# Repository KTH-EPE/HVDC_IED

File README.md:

# HVDC_IED
software and hardware for HVDC IED lab prototype

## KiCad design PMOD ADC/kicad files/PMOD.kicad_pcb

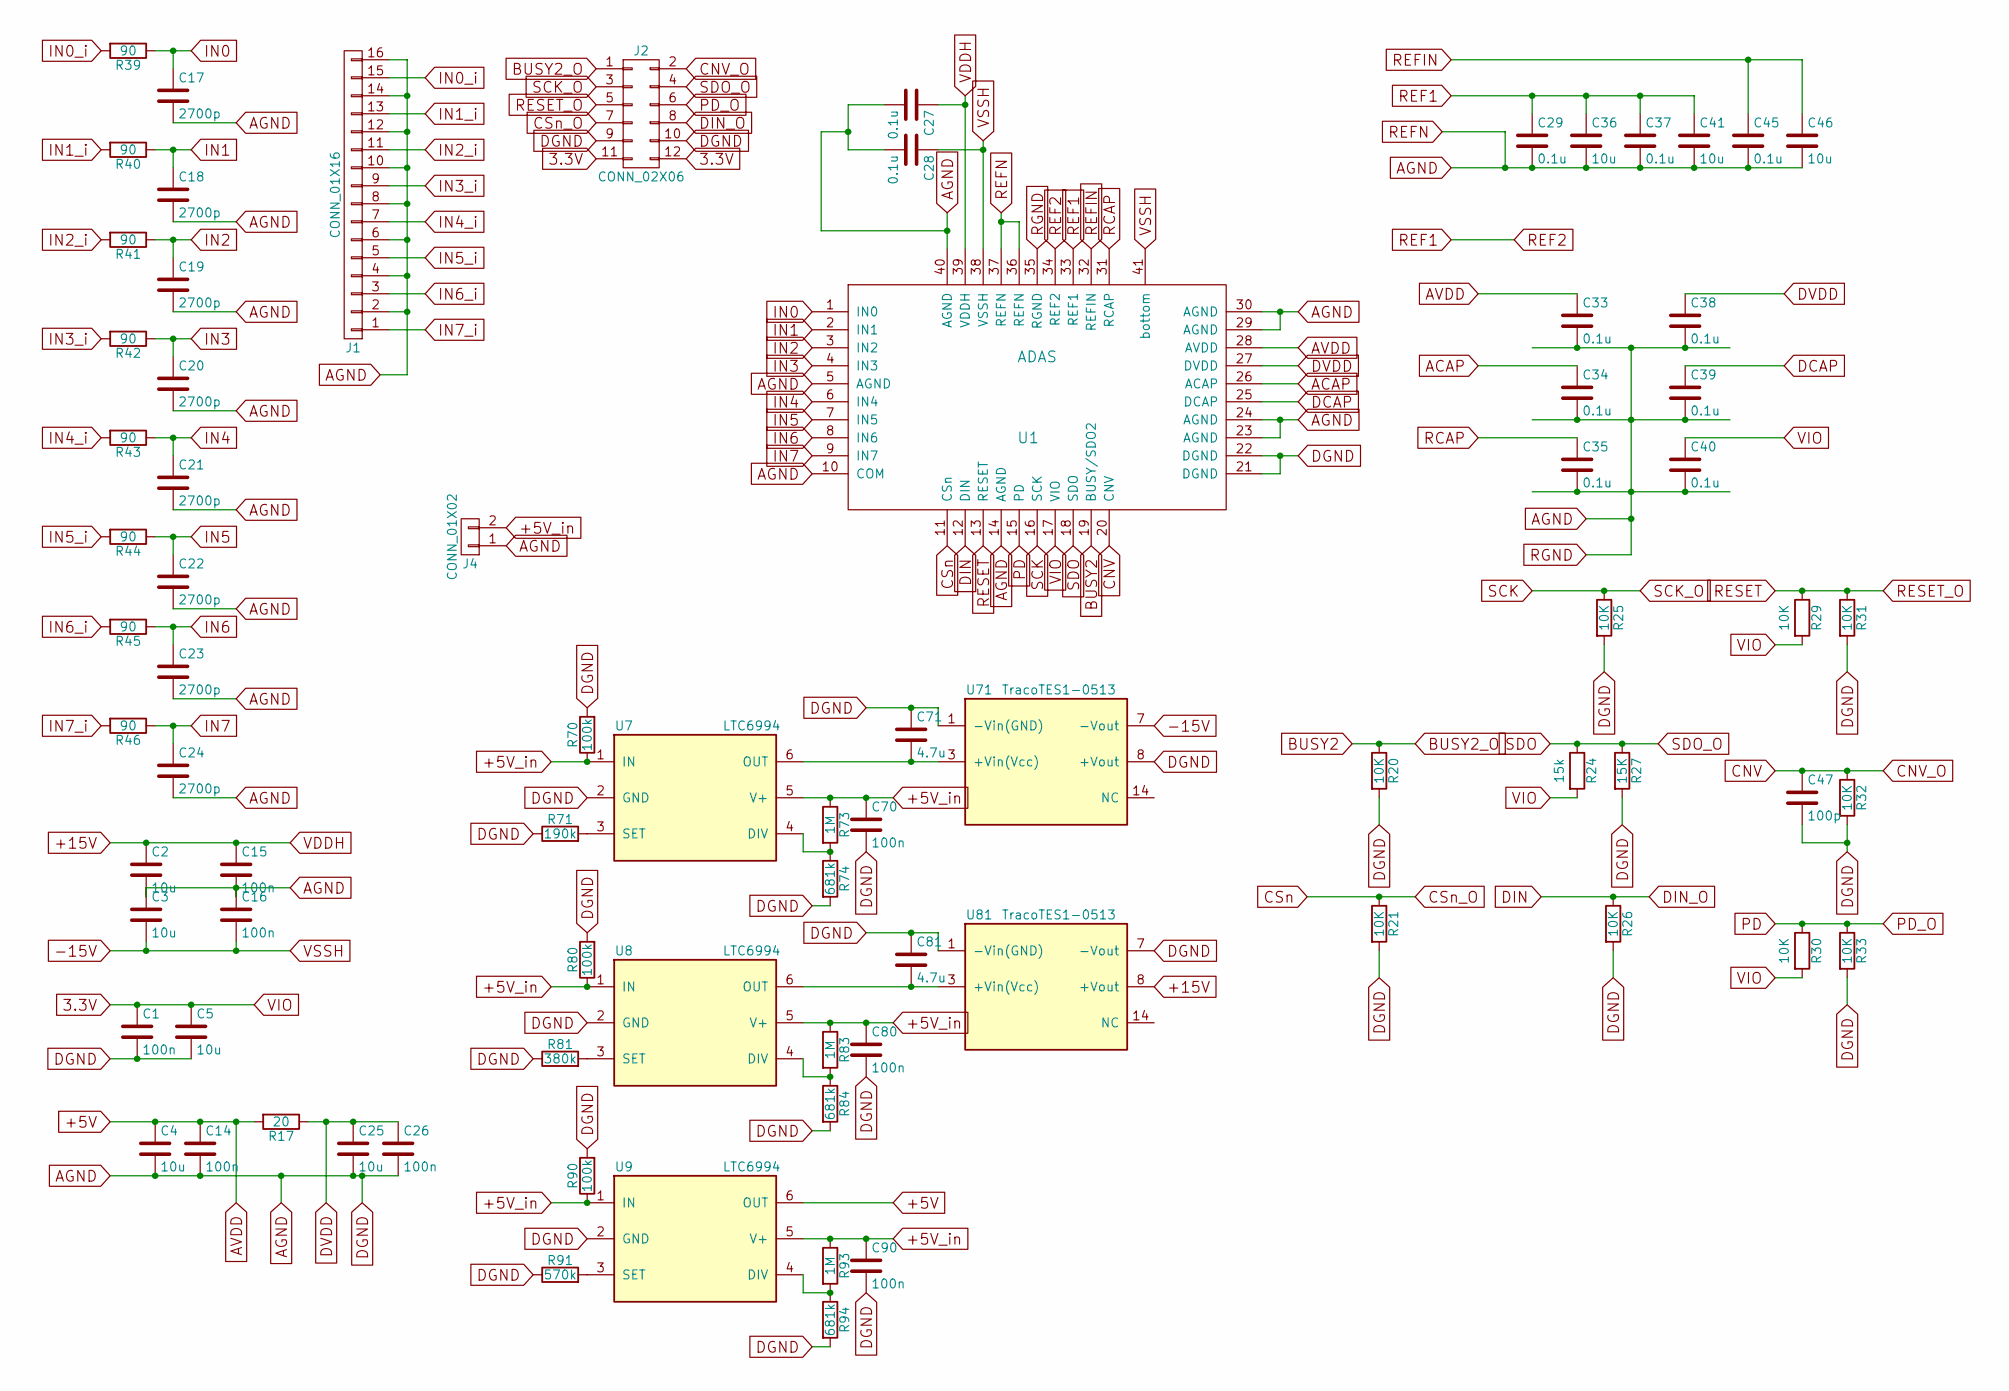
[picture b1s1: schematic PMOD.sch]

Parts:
C1, C14, C15, C16, C26, C70, C80, C90: 100n; C_1206_HandSoldering
C2, C3, C4, C5, C25, C36, C41, C46: 10u; C_1206_HandSoldering
C17, C18, C19, C20, C21, C22, C23, C24: 2700p; C_1206_HandSoldering
C27, C28, C29, C33, C34, C35, C37, C38, C39, C40, C45: 0.1u; C_1206_HandSoldering
C47: 100p; C_1206_HandSoldering
C71, C81: 4.7u; C_1206_HandSoldering
J1: CONN_01X16; Pin_Header_Angled_1x16_Pitch2.54mm
J2: CONN_02X06; Multicomp_MC9A_2x06x2.54mm_Straight
J4: CONN_01X02; Pin_Header_Angled_1x02_Pitch2.54mm
R17: 20; R_0603_HandSoldering
R20, R21, R25, R26, R29, R30, R31, R32, R33: 10K; R_0603_HandSoldering
R24: 15k; R_0603_HandSoldering
R27: 15K; R_0603_HandSoldering
R39, R40, R41, R42, R43, R44, R45, R46: 90; R_0603_HandSoldering
R70, R80, R90: 100k; R_0603_HandSoldering
R71: 190k; R_0603_HandSoldering
R73, R83, R93: 1M; R_0603_HandSoldering
R74, R84, R94: 681k; R_0603_HandSoldering
R81: 380k; R_0603_HandSoldering
R91: 570k; R_0603_HandSoldering
U1: ADAS; QFN-40-1EP_6x6mm_Pitch0.5mm
U7, U8, U9: LTC6994; TSOT-23-6_HandSoldering
U71, U81: TracoTES1-0513; DCDC-Conv_TRACO_TES-1SM

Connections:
3.3V: C1.1, C5.1, C40.1, J2.11, J2.12, R24.2, R29.2, R30.2, U1.17 (VIO)
+5V: C4.1, C14.1, C33.1, R17.2, U1.28 (AVDD), U9.6 (OUT)
+5V_in: C70.1, C80.1, C90.1, J4.2, R70.1, R73.1, R80.1, R83.1, R90.1, R93.1, U7.1 (IN), U7.5 (V+), U8.1 (IN), U8.5 (V+), U9.1 (IN), U9.5 (V+)
+15V: C2.1, C15.1, C27.1, U1.39 (VDDH), U81.8 (+Vout)
-15V: C3.2, C16.2, C28.1, U1.38 (VSSH), U1.41 (bottom), U71.7 (-Vout)
ACAP: C34.1, U1.26 (ACAP)
AGND: C1.2, C2.2, C3.1, C4.2, C5.2, C14.2, C15.2, C16.1, C17.2, C18.2, C19.2, C20.2, C21.2, C22.2, C23.2, C24.2, C25.2, C26.2, C27.2, C28.2, C29.2, C33.2, C34.2, C35.2, C36.2, C37.2, C38.2, C39.2, C40.2, C41.2, C45.2, C46.2, C47.2, C70.2, C71.1, C80.2, C81.1, C90.2, J1.2, J1.4, J1.6, J1.8, J1.10, J1.12, J1.14, J1.16, J2.9, J2.10, J4.1, R20.2, R21.2, R25.2, R26.2, R27.2, R31.2, R32.2, R33.2, R70.2, R71.1, R74.2, R80.2, R81.1, R84.2, R90.2, R91.1, R94.2, U1.5 (AGND), U1.10 (COM), U1.14 (AGND), U1.21 (DGND), U1.22 (DGND), U1.23 (AGND), U1.24 (AGND), U1.29 (AGND), U1.30 (AGND), U1.35 (RGND), U1.36 (REFN), U1.37 (REFN), U1.40 (AGND), U7.2 (GND), U8.2 (GND), U9.2 (GND), U71.1 (-Vin(GND)), U71.8 (+Vout), U81.1 (-Vin(GND)), U81.7 (-Vout)
BUSY2: J2.1, R20.1, U1.19 (BUSY/SDO2)
CNV: C47.1, J2.2, R32.1, U1.20 (CNV)
CSn: J2.7, R21.1, U1.11 (CSn)
DCAP: C39.1, U1.25 (DCAP)
DIN: J2.8, R26.1, U1.12 (DIN)
DVDD: C25.1, C26.1, C38.1, R17.1, U1.27 (DVDD)
IN0: C17.1, R39.1, U1.1 (IN0)
IN0_i: J1.15, R39.2
IN1: C18.1, R40.1, U1.2 (IN1)
IN1_i: J1.13, R40.2
IN2: C19.1, R41.1, U1.3 (IN2)
IN2_i: J1.11, R41.2
IN3: C20.1, R42.1, U1.4 (IN3)
IN3_i: J1.9, R42.2
IN4: C21.1, R43.1, U1.6 (IN4)
IN4_i: J1.7, R43.2
IN5: C22.1, R44.1, U1.7 (IN5)
IN5_i: J1.5, R44.2
IN6: C23.1, R45.1, U1.8 (IN6)
IN6_i: J1.3, R45.2
IN7: C24.1, R46.1, U1.9 (IN7)
IN7_i: J1.1, R46.2
unnamed: C71.2, U7.6 (OUT), U71.3 (+Vin(Vcc))
unnamed: C81.2, U8.6 (OUT), U81.3 (+Vin(Vcc))
unnamed: R71.2, U7.3 (SET)
unnamed: R73.2, R74.1, U7.4 (DIV)
unnamed: R81.2, U8.3 (SET)
unnamed: R83.2, R84.1, U8.4 (DIV)
unnamed: R91.2, U9.3 (SET)
unnamed: R93.2, R94.1, U9.4 (DIV)
PD: J2.6, R30.1, R33.1, U1.15 (PD)
RCAP: C35.1, U1.31 (RCAP)
REF1: C29.1, C36.1, C37.1, C41.1, U1.33 (REF1), U1.34 (REF2)
REFIN: C45.1, C46.1, U1.32 (REFIN)
RESET: J2.5, R29.1, R31.1, U1.13 (RESET)
SCK: J2.3, R25.1, U1.16 (SCK)
SDO: J2.4, R24.1, R27.1, U1.18 (SDO)

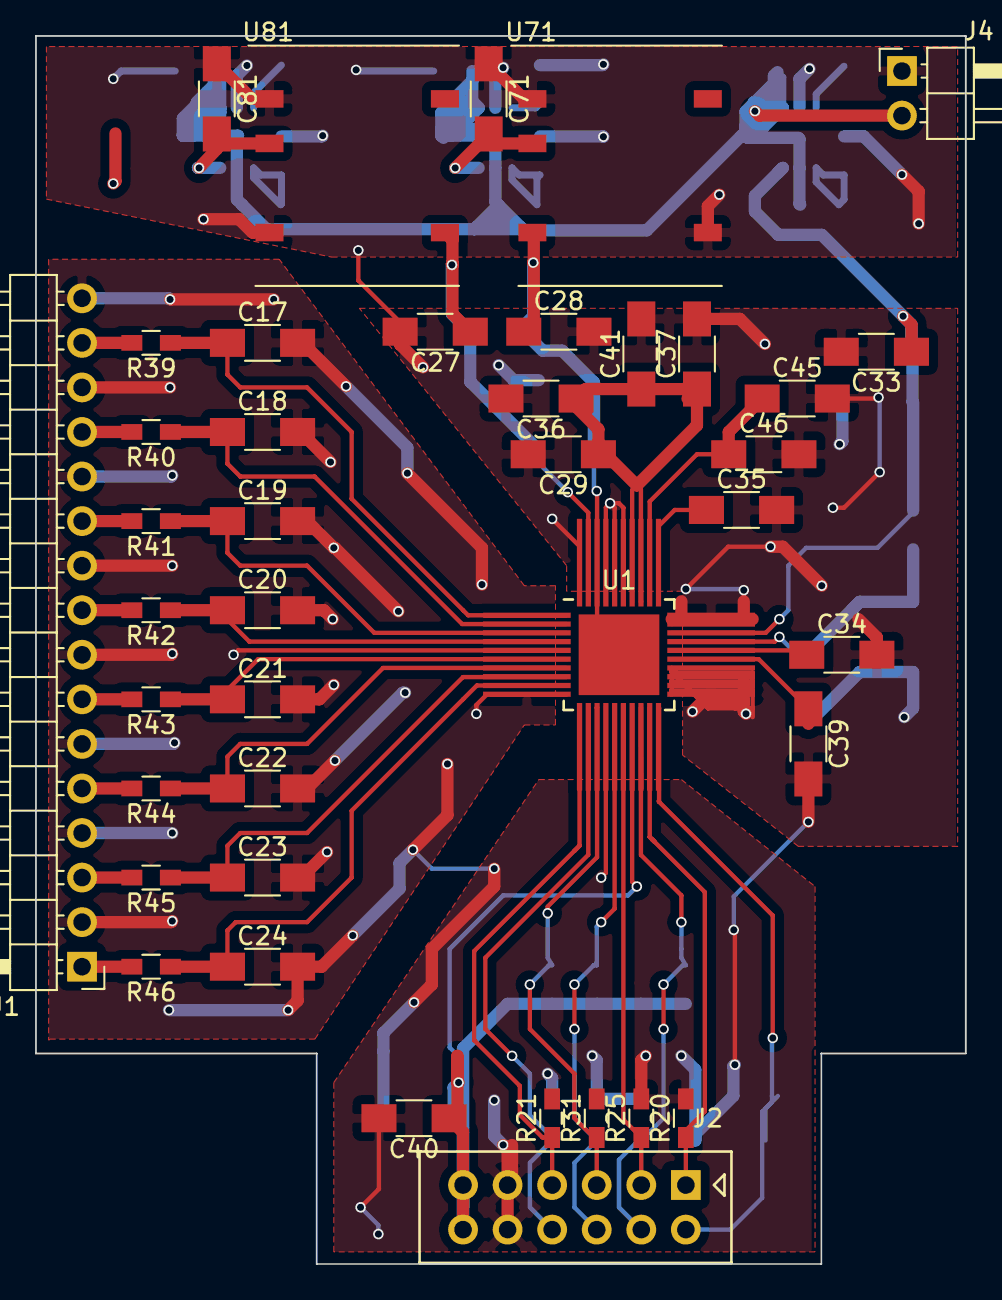
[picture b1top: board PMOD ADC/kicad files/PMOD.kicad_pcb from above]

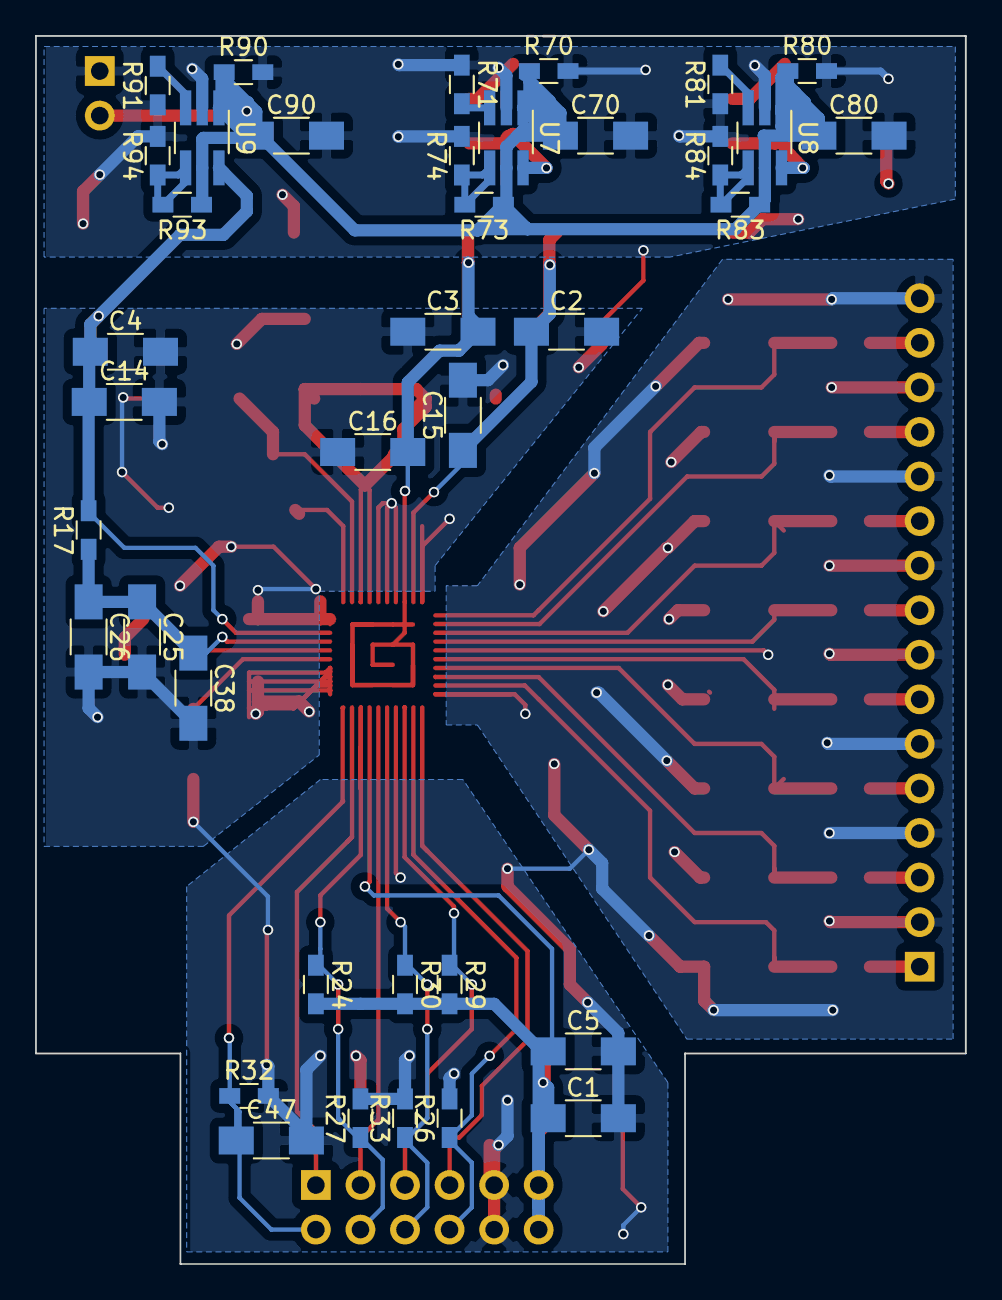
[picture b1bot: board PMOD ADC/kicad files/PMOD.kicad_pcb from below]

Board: 2 copper layers, 53.0 x 70.0 mm, 79 parts (38 on the bottom side), 44 nets.

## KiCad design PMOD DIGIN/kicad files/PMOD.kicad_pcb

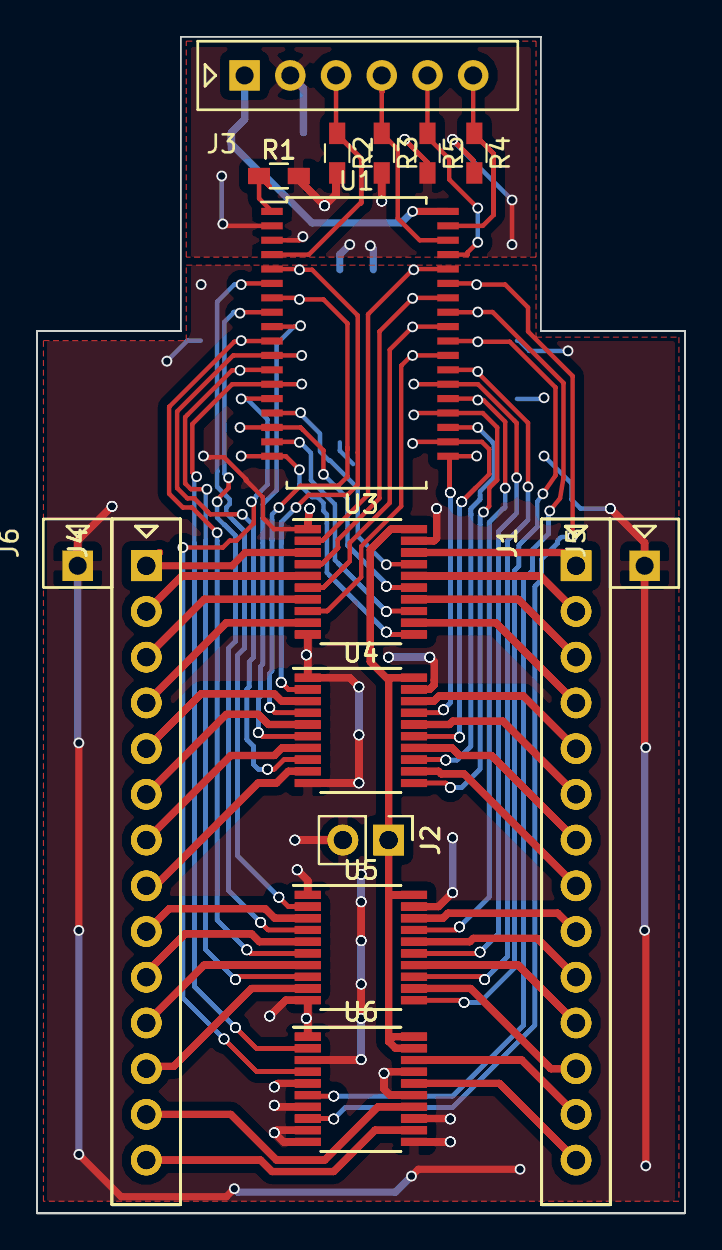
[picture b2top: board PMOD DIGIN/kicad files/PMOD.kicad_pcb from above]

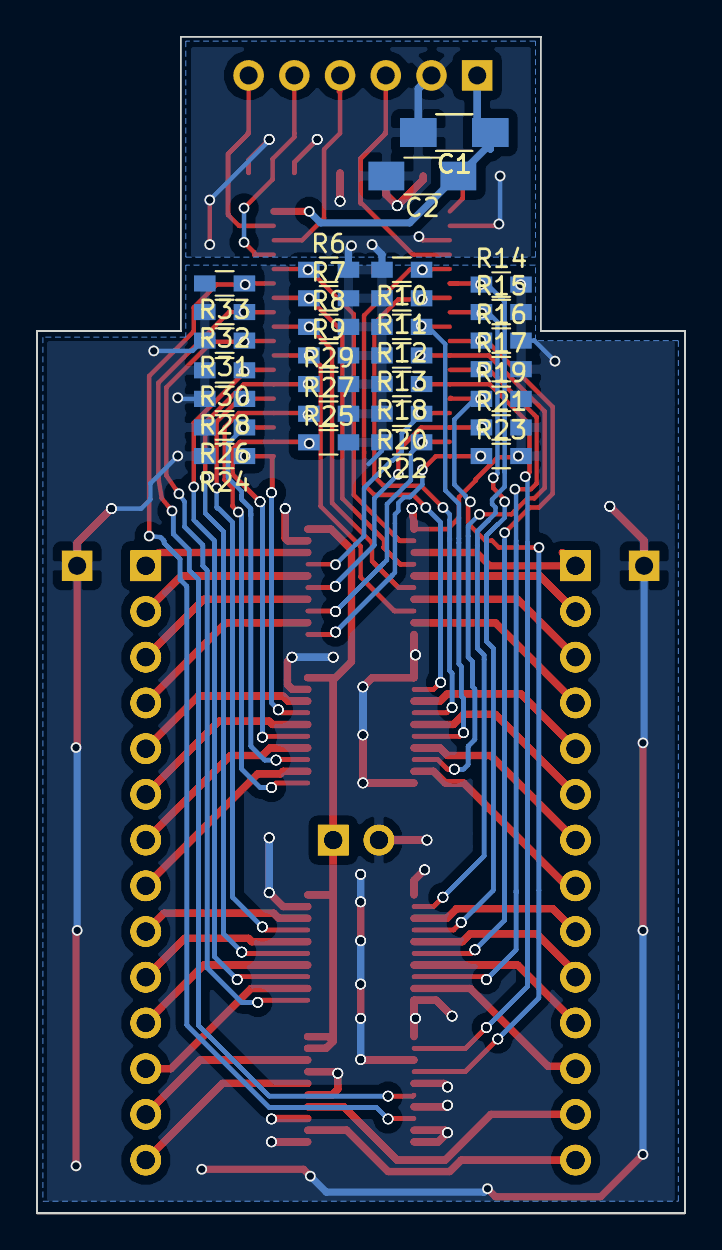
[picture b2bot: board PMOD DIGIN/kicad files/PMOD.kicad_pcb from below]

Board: 2 copper layers, 36.0 x 65.4 mm, 55 parts (31 on the bottom side), 64 nets.

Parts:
C1, C1#2: 1u; C_1206_HandSoldering
C2: 47n; C_1206_HandSoldering
J1, J1#2, J4, J4#2: CONN_01X14; Multicomp_MC9A_1x14x2.54mm_Straight
J2, J2#2: CONN_01X02_MALE; Pin_Header_Straight_1x02_Pitch2.54mm
J3: CONN_01X06; Multicomp_MC9A_2x06x2.54mm_Straight
J5, J6: CONN_01X01; Multicomp_MC9A_1x14x2.54mm_Straight
R1, R1#2: 39k; R_0603_HandSoldering
R2, R3, R4, R5, R6, R7, R8, R9, R10, R11, R12, R13, R14, R15, R16, R17, R18, R19, R20, R21, R22, R23, R24, R25, R26, R27, R28, R29, R30, R31, R32, R33: 10k; R_0603_HandSoldering
U1: MAX7301; SSOP-63_7.5x15.9mm_Pitch0.635mm
U3, U3#2, U4, U4#2, U5, U5#2, U6, U6#2: MC74VHCT244A; TSSOP-20_4.4x6.5mm_Pitch0.65mm

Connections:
+3V3: C1.1, C1#2.1, C2.1, J3.1, U1.36
+5V: J2.1, J2#2.1, U3.20, U3#2.20, U4.20, U4#2.20, U5.20, U5#2.20, U6.19, U6.20, U6#2.19, U6#2.20
GND: C1.2, C1#2.2, C2.2, J2.2, J2#2.2, J3.2, J5.1, J6.1, R1.2, R1#2.2, R2.2, R3.2, R4.2, R5.2, R6.2, R7.2, R8.2, R9.2, R10.2, R11.2, R12.2, R13.2, R14.2, R15.2, R16.2, R17.2, R18.2, R19.2, R20.2, R21.2, R22.2, R23.2, R24.2, R25.2, R26.2, R27.2, R28.2, R29.2, R30.2, R31.2, R32.2, R33.2, U1.2, U1.3, U3.1, U3.10, U3.19, U3#2.1, U3#2.10, U3#2.19, U4.1, U4.10, U4.19, U4#2.1, U4#2.10, U4#2.19, U5.1, U5.10, U5.19, U5#2.1, U5#2.10, U5#2.19, U6.1, U6.3, U6.5, U6.7, U6.9, U6.10, U6.11, U6.13, U6.15, U6.17, U6#2.1, U6#2.3, U6#2.5, U6#2.7, U6#2.9, U6#2.10, U6#2.11, U6#2.13, U6#2.15, U6#2.17
unnamed: J3.3, R2.1, U1.4
unnamed: J3.4, R3.1, U1.34
unnamed: J3.5, R5.1, U1.33
unnamed: J3.6, R4.1, U1.35
unnamed: R1.1, R1#2.1, U1.1
sig1: J1.1, J1#2.1, U3.18, U3#2.18
sig2: J1.2, J1#2.2, U3.16, U3#2.16
sig3: J1.3, J1#2.3, U3.14, U3#2.14
sig4: J1.4, J1#2.4, U3.12, U3#2.12
sig5: J1.5, J1#2.5, U4.18, U4#2.18
sig6: J1.6, J1#2.6, U4.16, U4#2.16
sig7: J1.7, J1#2.7, U4.14, U4#2.14
sig8: J1.8, J1#2.8, U4.12, U4#2.12
sig9: J1.9, J1#2.9, U5.18, U5#2.18
sig10: J1.10, J1#2.10, U5.16, U5#2.16
sig11: J1.11, J1#2.11, U5.14, U5#2.14
sig12: J1.12, J1#2.12, U5.12, U5#2.12
sig13: J1.13, J1#2.13, U6.18, U6#2.18
sig14: J1.14, J1#2.14, U6.16, U6#2.16
sig15: J4.1, J4#2.1, U3.3, U3#2.3
sig16: J4.2, J4#2.2, U3.5, U3#2.5
sig17: J4.3, J4#2.3, U3.7, U3#2.7
sig18: J4.4, J4#2.4, U3.9, U3#2.9
sig19: J4.5, J4#2.5, U4.3, U4#2.3
sig20: J4.6, J4#2.6, U4.5, U4#2.5
sig21: J4.7, J4#2.7, U4.7, U4#2.7
sig22: J4.8, J4#2.8, U4.9, U4#2.9
sig23: J4.9, J4#2.9, U5.3, U5#2.3
sig24: J4.10, J4#2.10, U5.5, U5#2.5
sig25: J4.11, J4#2.11, U5.7, U5#2.7
sig26: J4.12, J4#2.12, U5.9, U5#2.9
sig27: J4.13, J4#2.13, U6.14, U6#2.14
sig28: J4.14, J4#2.14, U6.12, U6#2.12
sig_1: R6.1, U1.32, U3.2, U3#2.2
sig_2: R7.1, U1.30, U3.4, U3#2.4
sig_3: R8.1, U1.28, U3.6, U3#2.6
sig_4: R9.1, U1.26, U3.8, U3#2.8
sig_5: R10.1, U1.5, U4.2, U4#2.2
sig_6: R11.1, U1.7, U4.4, U4#2.4
sig_7: R12.1, U1.9, U4.6, U4#2.6
sig_8: R13.1, U1.11, U4.8, U4#2.8
sig_9: R14.1, U1.6, U5.2, U5#2.2
sig_10: R15.1, U1.8, U5.4, U5#2.4
sig_11: R16.1, U1.10, U5.6, U5#2.6
sig_12: R17.1, U1.12, U5.8, U5#2.8
sig_13: R18.1, U1.13, U6.2, U6#2.2
sig_14: R19.1, U1.14, U6.4, U6#2.4
sig_15: R20.1, U1.15, U3.17, U3#2.17
sig_16: R21.1, U1.16, U3.15, U3#2.15
sig_17: R22.1, U1.17, U3.13, U3#2.13
sig_18: R23.1, U1.18, U3.11, U3#2.11
sig_19: R24.1, U1.19, U4.17, U4#2.17
sig_20: R25.1, U1.20, U4.15, U4#2.15
sig_21: R26.1, U1.21, U4.13, U4#2.13
sig_22: R27.1, U1.22, U4.11, U4#2.11
sig_23: R28.1, U1.23, U5.17, U5#2.17
sig_24: R29.1, U1.24, U5.15, U5#2.15
sig_25: R30.1, U1.25, U5.13, U5#2.13
sig_26: R31.1, U1.27, U5.11, U5#2.11
sig_27: R32.1, U1.29, U6.6, U6#2.6
sig_28: R33.1, U1.31, U6.8, U6#2.8

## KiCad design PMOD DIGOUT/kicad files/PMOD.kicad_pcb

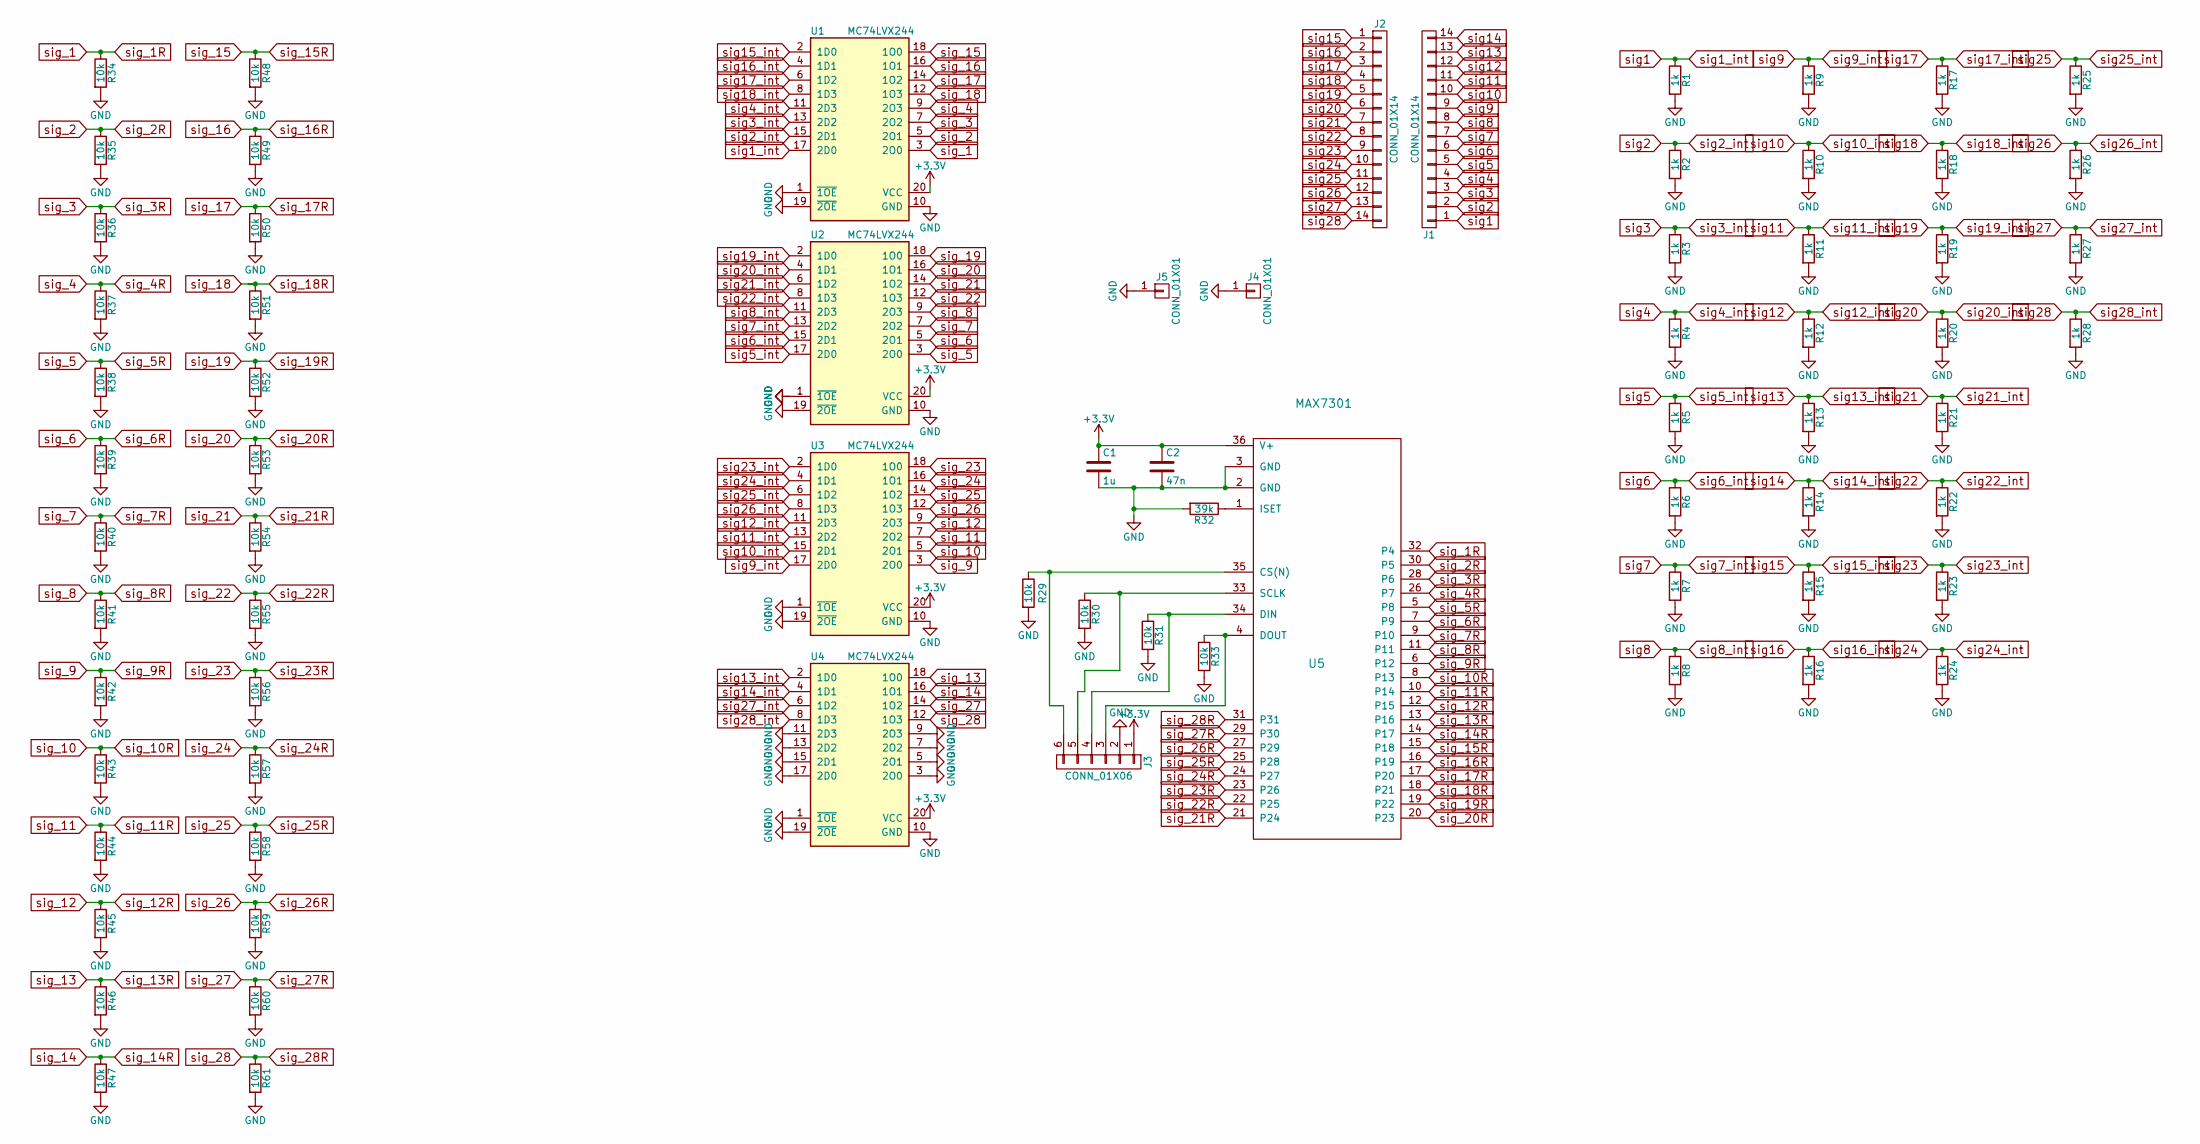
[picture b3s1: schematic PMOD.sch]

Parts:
C1: 1u; C_1206_HandSoldering
C2: 47n; C_1206_HandSoldering
J1, J2: CONN_01X14; Multicomp_MC9A_1x14x2.54mm_Straight
J3: CONN_01X06
J4, J5: CONN_01X01
R1, R2, R3, R4, R5, R6, R7, R8, R9, R10, R11, R12, R13, R14, R15, R16, R17, R18, R19, R20, R21, R22, R23, R24, R25, R26, R27, R28: 1k; R_0603_HandSoldering
R29, R30, R31, R33, R34, R35, R36, R37, R38, R39, R40, R41, R42, R43, R44, R45, R46, R47, R48, R49, R50, R51, R52, R53, R54, R55, R56, R57, R58, R59, R60, R61: 10k; R_0603_HandSoldering
R32: 39k; R_0603_HandSoldering
U1, U2, U3, U4: MC74LVX244; TSSOP-20_4.4x6.5mm_Pitch0.65mm
U5: MAX7301; SSOP-63_7.5x15.9mm_Pitch0.635mm

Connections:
+3V3: C1.1, C2.1, J3.1, U1.20 (VCC), U2.20 (VCC), U3.20 (VCC), U4.20 (VCC), U5.36 (V+)
GND: C1.2, C2.2, J3.2, J4.1, J5.1, R1.2, R2.2, R3.2, R4.2, R5.2, R6.2, R7.2, R8.2, R9.2, R10.2, R11.2, R12.2, R13.2, R14.2, R15.2, R16.2, R17.2, R18.2, R19.2, R20.2, R21.2, R22.2, R23.2, R24.2, R25.2, R26.2, R27.2, R28.2, R29.2, R30.2, R31.2, R32.2, R33.2, R34.2, R35.2, R36.2, R37.2, R38.2, R39.2, R40.2, R41.2, R42.2, R43.2, R44.2, R45.2, R46.2, R47.2, R48.2, R49.2, R50.2, R51.2, R52.2, R53.2, R54.2, R55.2, R56.2, R57.2, R58.2, R59.2, R60.2, R61.2, U1.1 (~1OE~), U1.10 (GND), U1.19 (~2OE~), U2.1 (~1OE~), U2.10 (GND), U2.19 (~2OE~), U3.1 (~1OE~), U3.10 (GND), U3.19 (~2OE~), U4.1 (~1OE~), U4.3 (2O0), U4.5 (2O1), U4.7 (2O2), U4.9 (2O3), U4.10 (GND), U4.11 (2D3), U4.13 (2D2), U4.15 (2D1), U4.17 (2D0), U4.19 (~2OE~), U5.2 (GND), U5.3 (GND)
unnamed: J3.3, R33.1, U5.4 (DOUT)
unnamed: J3.4, R31.1, U5.34 (DIN)
unnamed: J3.5, R30.1, U5.33 (SCLK)
unnamed: J3.6, R29.1, U5.35 (CS(N))
unnamed: R32.1, U5.1 (ISET)
sig1: J1.1, R1.1, U1.17 (2D0)
sig2: J1.2, R2.1, U1.15 (2D1)
sig3: J1.3, R3.1, U1.13 (2D2)
sig4: J1.4, R4.1, U1.11 (2D3)
sig5: J1.5, R5.1, U2.17 (2D0)
sig6: J1.6, R6.1, U2.15 (2D1)
sig7: J1.7, R7.1, U2.13 (2D2)
sig8: J1.8, R8.1, U2.11 (2D3)
sig9: J1.9, R9.1, U3.17 (2D0)
sig10: J1.10, R10.1, U3.15 (2D1)
sig11: J1.11, R11.1, U3.13 (2D2)
sig12: J1.12, R12.1, U3.11 (2D3)
sig13: J1.13, R13.1, U4.2 (1D0)
sig14: J1.14, R14.1, U4.4 (1D1)
sig15: J2.1, R15.1, U1.2 (1D0)
sig16: J2.2, R16.1, U1.4 (1D1)
sig17: J2.3, R17.1, U1.6 (1D2)
sig18: J2.4, R18.1, U1.8 (1D3)
sig19: J2.5, R19.1, U2.2 (1D0)
sig20: J2.6, R20.1, U2.4 (1D1)
sig21: J2.7, R21.1, U2.6 (1D2)
sig22: J2.8, R22.1, U2.8 (1D3)
sig23: J2.9, R23.1, U3.2 (1D0)
sig24: J2.10, R24.1, U3.4 (1D1)
sig25: J2.11, R25.1, U3.6 (1D2)
sig26: J2.12, R26.1, U3.8 (1D3)
sig27: J2.13, R27.1, U4.6 (1D2)
sig28: J2.14, R28.1, U4.8 (1D3)
sig_1: R34.1, U1.3 (2O0), U5.32 (P4)
sig_2: R35.1, U1.5 (2O1), U5.30 (P5)
sig_3: R36.1, U1.7 (2O2), U5.28 (P6)
sig_4: R37.1, U1.9 (2O3), U5.26 (P7)
sig_5: R38.1, U2.3 (2O0), U5.5 (P8)
sig_6: R39.1, U2.5 (2O1), U5.7 (P9)
sig_7: R40.1, U2.7 (2O2), U5.9 (P10)
sig_8: R41.1, U2.9 (2O3), U5.11
sig_9: R42.1, U3.3 (2O0), U5.6 (P12)
sig_10: R43.1, U3.5 (2O1), U5.8 (P13)
sig_11: R44.1, U3.7 (2O2), U5.10 (P14)
sig_12: R45.1, U3.9 (2O3), U5.12 (P15)
sig_13: R46.1, U4.18 (1O0), U5.13 (P16)
sig_14: R47.1, U4.16 (1O1), U5.14 (P17)
sig_15: R48.1, U1.18 (1O0), U5.15 (P18)
sig_16: R49.1, U1.16 (1O1), U5.16 (P19)
sig_17: R50.1, U1.14 (1O2), U5.17 (P20)
sig_18: R51.1, U1.12 (1O3), U5.18 (P21)
sig_19: R52.1, U2.18 (1O0), U5.19 (P22)
sig_20: R53.1, U2.16 (1O1), U5.20 (P23)
sig_21: R54.1, U2.14 (1O2), U5.21 (P24)
sig_22: R55.1, U2.12 (1O3), U5.22 (P25)
sig_23: R56.1, U3.18 (1O0), U5.23 (P26)
sig_24: R57.1, U3.16 (1O1), U5.24 (P27)
sig_25: R58.1, U3.14 (1O2), U5.25 (P28)
sig_26: R59.1, U3.12 (1O3), U5.27 (P29)
sig_27: R60.1, U4.14 (1O2), U5.29 (P30)
sig_28: R61.1, U4.12 (1O3), U5.31

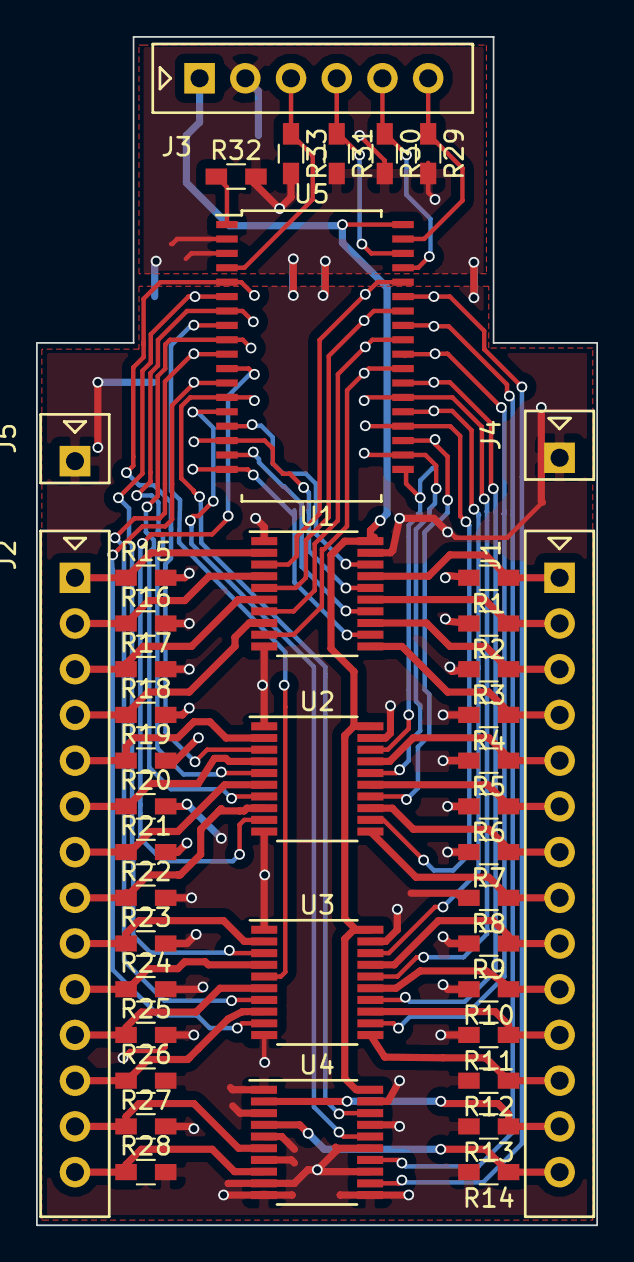
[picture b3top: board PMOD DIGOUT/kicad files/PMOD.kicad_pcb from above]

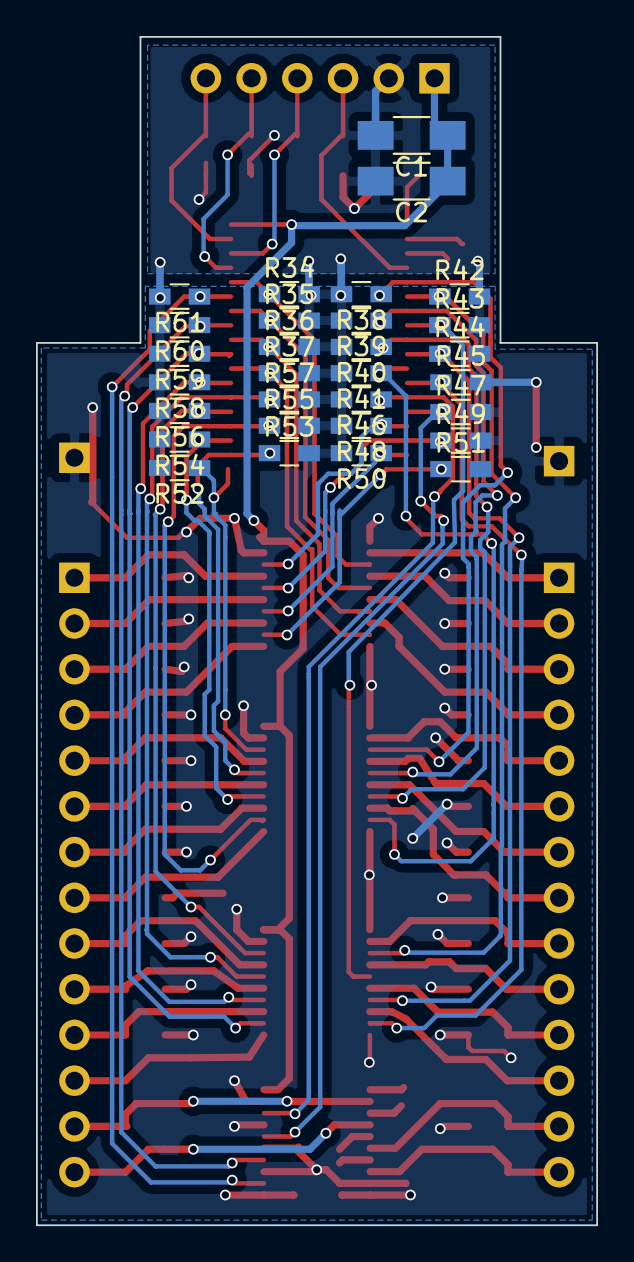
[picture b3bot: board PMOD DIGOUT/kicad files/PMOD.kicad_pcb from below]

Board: 2 copper layers, 31.1 x 66.0 mm, 73 parts (30 on the bottom side), 63 nets.

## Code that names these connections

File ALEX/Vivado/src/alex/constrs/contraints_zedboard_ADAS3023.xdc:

# ----------------------------------------------------------------------------
# JA Pmod - Bank 13 - ADC 2
# ---------------------------------------------------------------------------- 
set_property PACKAGE_PIN Y11  [get_ports busy_1]; # "JA1"
set_property PACKAGE_PIN AA11 [get_ports sck_1];  # "JA2"
set_property PACKAGE_PIN Y10  [get_ports reset_1];# "JA3"
set_property PACKAGE_PIN AA9  [get_ports csn_1];  # "JA4"
set_property PACKAGE_PIN AB11 [get_ports cnv_1];  # "JA7"
set_property PACKAGE_PIN AB10 [get_ports sdo_1];  # "JA8"
set_property PACKAGE_PIN AB9  [get_ports pd_1];   # "JA9"
set_property PACKAGE_PIN AA8  [get_ports din_1];  # "JA10"

set_property IOSTANDARD LVCMOS33 [get_ports busy_1]
set_property IOSTANDARD LVCMOS33 [get_ports sck_1]
set_property IOSTANDARD LVCMOS33 [get_ports reset_1]
set_property IOSTANDARD LVCMOS33 [get_ports csn_1]
set_property IOSTANDARD LVCMOS33 [get_ports cnv_1]
set_property IOSTANDARD LVCMOS33 [get_ports sdo_1]
set_property IOSTANDARD LVCMOS33 [get_ports pd_1]
set_property IOSTANDARD LVCMOS33 [get_ports din_1]


# ----------------------------------------------------------------------------
# JB Pmod - Bank 13 - ADC 1
# ---------------------------------------------------------------------------- 
set_property PACKAGE_PIN W12 [get_ports busy]; # "JB1"
set_property PACKAGE_PIN W11 [get_ports sck];  # "JB2"
set_property PACKAGE_PIN V10 [get_ports reset];# "JB3"
set_property PACKAGE_PIN W8  [get_ports csn];  # "JB4"
set_property PACKAGE_PIN V12 [get_ports cnv];  # "JB7"
set_property PACKAGE_PIN W10 [get_ports sdo];  # "JB8"
set_property PACKAGE_PIN V9  [get_ports pd];   # "JB9"
set_property PACKAGE_PIN V8  [get_ports din];  # "JB10"

set_property IOSTANDARD LVCMOS33 [get_ports busy]
set_property IOSTANDARD LVCMOS33 [get_ports sck]
set_property IOSTANDARD LVCMOS33 [get_ports reset]
set_property IOSTANDARD LVCMOS33 [get_ports csn]
set_property IOSTANDARD LVCMOS33 [get_ports cnv]
set_property IOSTANDARD LVCMOS33 [get_ports sdo]
set_property IOSTANDARD LVCMOS33 [get_ports pd]
set_property IOSTANDARD LVCMOS33 [get_ports din]


# ----------------------------------------------------------------------------
# JC Pmod - Bank 13 - IED front panel LEDs
# ---------------------------------------------------------------------------- 
set_property PACKAGE_PIN AB7 [get_ports {trip_led_front[0]}];  # "JC1_P"
set_property PACKAGE_PIN AB6 [get_ports {trip_led_front[1]}];  # "JC1_N"
set_property PACKAGE_PIN Y4  [get_ports {trip_led_front[2]}];  # "JC2_P"
set_property PACKAGE_PIN AA4 [get_ports {trip_led_front[3]}];  # "JC2_N"
set_property PACKAGE_PIN R6  [get_ports {trip_led_front[4]}];  # "JC3_P"
set_property PACKAGE_PIN T6  [get_ports {trip_led_front[5]}];  # "JC3_N"
set_property PACKAGE_PIN T4  [get_ports {trip_led_front[6]}];  # "JC4_P"
set_property PACKAGE_PIN U4  [get_ports {trip_led_front[7]}];  # "JC4_N"


set_property IOSTANDARD LVCMOS33 [get_ports {trip_led_front[0]}];
set_property IOSTANDARD LVCMOS33 [get_ports {trip_led_front[1]}];
set_property IOSTANDARD LVCMOS33 [get_ports {trip_led_front[2]}];
set_property IOSTANDARD LVCMOS33 [get_ports {trip_led_front[3]}];
set_property IOSTANDARD LVCMOS33 [get_ports {trip_led_front[4]}];
set_property IOSTANDARD LVCMOS33 [get_ports {trip_led_front[5]}];
set_property IOSTANDARD LVCMOS33 [get_ports {trip_led_front[6]}];
set_property IOSTANDARD LVCMOS33 [get_ports {trip_led_front[7]}];


# ----------------------------------------------------------------------------
# JD Pmod - Bank 13 - digital input and output card
# ---------------------------------------------------------------------------- 
# digital in, upper row
set_property PACKAGE_PIN V7 [get_ports {MAX1_CS}];    # "JD1_P" -- clock for MAX
set_property PACKAGE_PIN W7 [get_ports {MAX1_SCK}];   # "JD1_N" -- chip select for MAX
set_property PACKAGE_PIN V5 [get_ports {MAX1_DIN}];   # "JD2_P" -- data coming from MAX
set_property PACKAGE_PIN V4 [get_ports {MAX1_DOUT}];  # "JD2_N" -- command bytes for MAX

# digital out, lower row
set_property PACKAGE_PIN W6 [get_ports {MAX2_CS}];   # "JD3_P"
set_property PACKAGE_PIN W5 [get_ports {MAX2_SCK}];  # "JD3_N"
set_property PACKAGE_PIN U6 [get_ports {MAX2_DIN}];  # "JD4_P"
set_property PACKAGE_PIN U5 [get_ports {MAX2_DOUT}]; # "JD4_N"

set_property IOSTANDARD LVCMOS33 [get_ports {MAX1_CS}];
set_property IOSTANDARD LVCMOS33 [get_ports {MAX1_SCK}];
set_property IOSTANDARD LVCMOS33 [get_ports {MAX1_DIN}];
set_property IOSTANDARD LVCMOS33 [get_ports {MAX1_DOUT}];
set_property IOSTANDARD LVCMOS33 [get_ports {MAX2_CS}];
set_property IOSTANDARD LVCMOS33 [get_ports {MAX2_SCK}];
set_property IOSTANDARD LVCMOS33 [get_ports {MAX2_DIN}];
set_property IOSTANDARD LVCMOS33 [get_ports {MAX2_DOUT}];

# ----------------------------------------------------------------------------
# User LEDs - Bank 33 - indicate trip signals
# ---------------------------------------------------------------------------- 
set_property PACKAGE_PIN T22 [get_ports {trip_led_board[0]}];  # "LD0"
set_property PACKAGE_PIN T21 [get_ports {trip_led_board[1]}];  # "LD1"
set_property PACKAGE_PIN U22 [get_ports {trip_led_board[2]}];  # "LD2"
set_property PACKAGE_PIN U21 [get_ports {trip_led_board[3]}];  # "LD3"
set_property PACKAGE_PIN V22 [get_ports {trip_led_board[4]}];  # "LD4"
set_property PACKAGE_PIN W22 [get_ports {trip_led_board[5]}];  # "LD5"
set_property PACKAGE_PIN U19 [get_ports {trip_led_board[6]}];  # "LD6"
set_property PACKAGE_PIN U14 [get_ports {trip_led_board[7]}];  # "LD7"

set_property IOSTANDARD LVCMOS33 [get_ports {trip_led_board[0]}];
set_property IOSTANDARD LVCMOS33 [get_ports {trip_led_board[1]}];
set_property IOSTANDARD LVCMOS33 [get_ports {trip_led_board[2]}];
set_property IOSTANDARD LVCMOS33 [get_ports {trip_led_board[3]}];
set_property IOSTANDARD LVCMOS33 [get_ports {trip_led_board[4]}];
set_property IOSTANDARD LVCMOS33 [get_ports {trip_led_board[5]}];
set_property IOSTANDARD LVCMOS33 [get_ports {trip_led_board[6]}];
set_property IOSTANDARD LVCMOS33 [get_ports {trip_led_board[7]}];

# ----------------------------------------------------------------------------
# FMC Header
# ----------------------------------------------------------------------------
set_property PACKAGE_PIN G15 [get_ports TX]
set_property IOSTANDARD LVCMOS33 [get_ports TX]
set_property PULLUP true [get_ports TX]

set_property PACKAGE_PIN R19 [get_ports RX] 
#R19 on J8-1 works, receiver IP works
set_property IOSTANDARD LVCMOS33 [get_ports RX]
#set_property PULLUP true [get_ports RX]
# ----------------------------------------------------------------------------
# Enabling RS485 Transceiver (Always turned ON)
# ----------------------------------------------------------------------------
set_property PACKAGE_PIN C20 [get_ports TX_en]
set_property IOSTANDARD LVCMOS33 [get_ports TX_en]

set_property PACKAGE_PIN G16 [get_ports RX_en]
set_property IOSTANDARD LVCMOS33 [get_ports RX_en]

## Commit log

2020-02-10 Added the initial draft for IED assembling manual
2020-02-10 image upload
2020-02-10 removed unsused
2020-02-18 updated pictures for ADC, usb plugged in right port
2020-02-18 picture for LED connections
2020-02-25 updated manual
2020-02-25 rearranged sections
2020-02-26 change order of sections. power supply wiring after box is assembled
2020-02-26 more changes
